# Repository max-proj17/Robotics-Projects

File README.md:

# Robotics Projects

Welcome to my Robotics Projects repository!  
This collection includes various robotics systems, simulations, and embedded applications.

Each project has its own dedicated folder and wiki page for documentation, code, and resources.
Click the link below!

[Wiki](https://github.com/max-proj17/Robotics-Projects/wiki)

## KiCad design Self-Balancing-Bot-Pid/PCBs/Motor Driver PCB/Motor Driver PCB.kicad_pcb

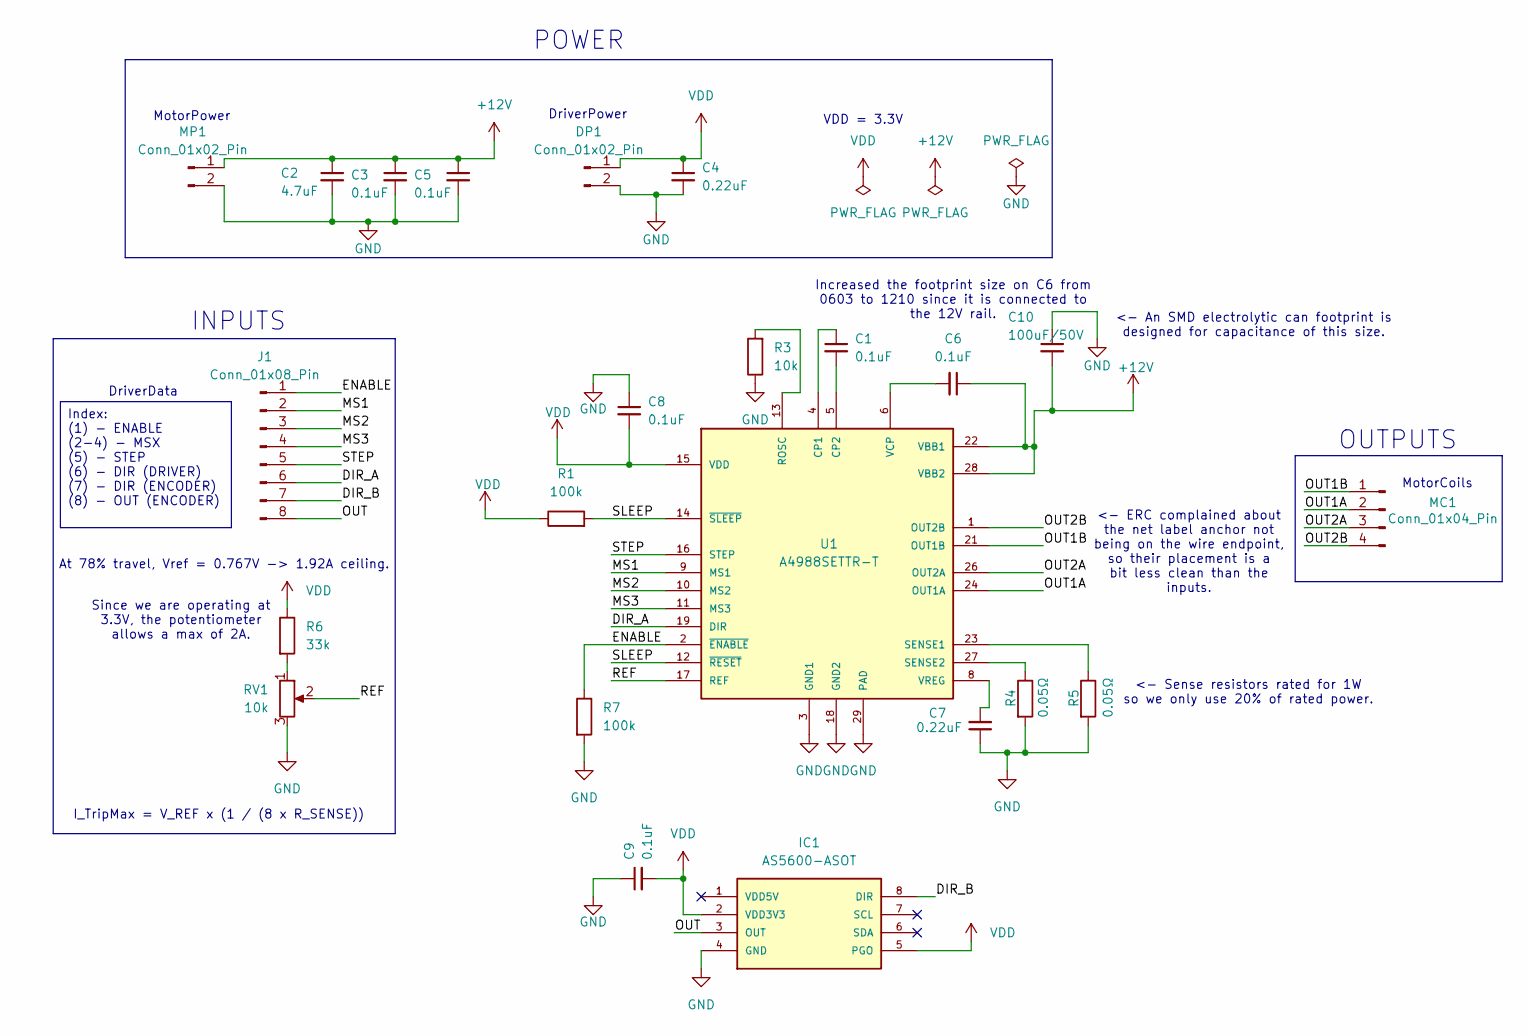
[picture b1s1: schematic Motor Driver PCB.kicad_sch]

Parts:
C1, C3, C5, C8, C9: 0.1uF; C_0603_1608Metric
C2: 4.7uF; C_0603_1608Metric
C4, C7: 0.22uF; C_0603_1608Metric
C6: 0.1uF; C_1210_3225Metric
C10: 100uF/50V; CP_Elec_8x10.5; MPN UWT1H101MNL1GS
DP1: Conn_01x02_Pin; JST_PH_B2B-PH-K_1x02_P2.00mm_Vertical
IC1: AS5600-ASOT; SOIC127P600X175-8N; MOUSER_PART_NUMBER 985-AS5600-ASOT
J1: Conn_01x08_Pin; JST_PH_B8B-PH-K_1x08_P2.00mm_Vertical
MC1: Conn_01x04_Pin; JST_PH_B4B-PH-K_1x04_P2.00mm_Vertical
MP1: Conn_01x02_Pin; JST_PH_B2B-PH-K_1x02_P2.00mm_Vertical
R1, R7: 100k; R_0603_1608Metric
R3: 10k; R_0603_1608Metric
R4, R5: 0.05Ω; R_2512_6332Metric; MPN WSL2512R0500FEA
R6: 33k; R_0603_1608Metric
RV1: 10k; Potentiometer_Bourns_3269W_Vertical
U1: A4988SETTR-T; QFN50P500X500X90-29N

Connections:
+12V: C2.1, C3.1, C5.1, C6.1, C10.2, MP1.1, U1.22 (VBB1), U1.28 (VBB2)
/DIR_A: J1.6, U1.19 (DIR)
/DIR_B: IC1.8 (DIR), J1.7
/ENABLE: J1.1, R7.1, U1.2 (~ENABLE)
/MS1: J1.2, U1.9 (MS1)
/MS2: J1.3, U1.10 (MS2)
/MS3: J1.4, U1.11 (MS3)
/OUT: IC1.3 (OUT), J1.8
/OUT1A: MC1.2, U1.24 (OUT1A)
/OUT1B: MC1.1, U1.21 (OUT1B)
/OUT2A: MC1.3, U1.26 (OUT2A)
/OUT2B: MC1.4, U1.1 (OUT2B)
/REF: RV1.2, U1.17 (REF)
/SLEEP: R1.2, U1.12 (~RESET), U1.14 (~SLEEP)
/STEP: J1.5, U1.16 (STEP)
GND: C2.2, C3.2, C4.2, C5.2, C7.1, C8.1, C9.1, C10.1, DP1.2, IC1.4 (GND), MP1.2, R3.1, R4.2, R5.2, R7.2, RV1.3, U1.3 (GND1), U1.18 (GND2), U1.29 (PAD)
unnamed: R6.2, RV1.1
unnamed: C1.1, U1.4 (CP1)
unnamed: C1.2, U1.5 (CP2)
unnamed: R3.2, U1.13 (ROSC)
unnamed: R5.1, U1.23 (SENSE1)
unnamed: R4.1, U1.27 (SENSE2)
unnamed: C6.2, U1.6 (VCP)
unnamed: C7.2, U1.8 (VREG)
VDD: C4.1, C8.2, C9.2, DP1.1, IC1.2 (VDD3V3), IC1.5 (PGO), R1.1, R6.1, U1.15 (VDD)

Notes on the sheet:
OUTPUTS
DriverData
MotorPower
At 78% travel, Vref = 0.767V -> 1.92A ceiling.
<- ERC complained about the net label anchor not being on the wire endpoint, so their placement is a bit less clean than the inputs.
<- Sense resistors rated for 1W so we only use 20% of rated power.
POWER
Increased the footprint size on C6 from 0603 to 1210 since it is connected to the 12V rail.
Since we are operating at 3.3V, the potentiometer allows a max of 2A.
DriverPower
MotorCoils
INPUTS
VDD = 3.3V
I_TripMax = V_REF x (1 / (8 x R_SENSE))
<- An SMD electrolytic can footprint is designed for capacitance of this size.
Index: (1) - ENABLE (2-4) - MSX (5) - STEP (6) - DIR (DRIVER) (7) - DIR (ENCODER) (8) - OUT (ENCODER)

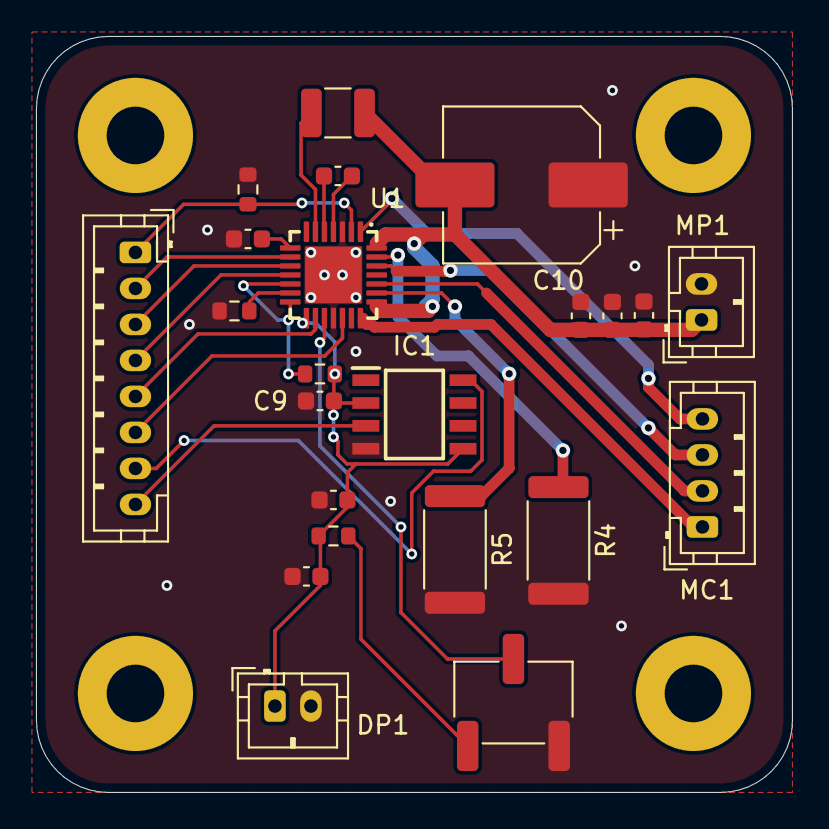
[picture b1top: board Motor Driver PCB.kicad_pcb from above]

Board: 2 copper layers, 42.0 x 42.0 mm, 27 parts (0 on the bottom side), 25 nets.

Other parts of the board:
Hole1, Hole2, Hole3, Hole4: MountingHole_3.2mm_M3_Pad

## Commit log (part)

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2025-04-11 Added arduino script to test driver and motor functionality at a high level
2025-04-12 Added encoder IC test. Had to add RC and software LPF because the sensor and onboard ADC is noisy
2025-04-12 Successfully integrated motor motion and encoder reading code. Next step is implementing FOC
2025-04-12 removed FOC for now because my motor driver does not have current sensing abilities. Will implement in the second version
2025-04-14 Started a test script for the IMU but the library is having issues
2025-04-15 Switched to a simpler library with a lot less overhead. Will not be using SPI or interrupts in this implementation. Maybe in v2 when I make compatible esp32s3 drivers myself.
2025-04-19 Working on chassis design now
2025-04-20 Started docker simulation environment creation
2025-04-20 Updated gitignore to remove uneeded files
2025-04-20 updated gitignore again with correct path
2025-04-20 Created working publisher and subscriber ros2 package within a docker container. Successfully setup development environment so I can run the docker containerfrom wsl in vscode on my host machine. Thi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
2025-04-22 Combined IMU and Encoder scripts into v1. Encodershave an offset value that I use so they are aligned with the IMU starting pitch
2025-04-23 Wrote xacro file and made it into a urdf. Still debugging why it isn't appearing in rviz
2025-04-24 Created urdf to resemble balancing bot size. Still need to fix the origins of the base, imu and encoders
2025-04-24 Completed full URDF with correct transforms
2025-04-24 realigned IMU
2025-04-25 My model loads in Gazebo! I also defined the mock hardware interface for the encoders and IMU.
2025-04-25 Slowing correcting the left and right wheel controllers. Focusing on the last couple dependency issues
2025-04-25 Almost have controllers working. Saving the progress I've made. Some params are in the wrong place
2025-04-28 edited dockerfile
2025-04-28 No more setup errors. Implementing controller node.
2025-04-29 refactored folder and package name
2025-04-29 Started kalman filter and PID implementation
2025-04-29 Fixed imu link probelm. Now just need to fix controller
2025-05-13 Added pause for the start and end of the gazebo simulation
2025-05-22 Fixed the imu publisher not starting issue. I just needed to use the default topic instead of my own. Focusing on fixing the timing of the physics now that the imu isnt the issue
2025-05-22 Forgot this file lol
2025-06-02 Starting attempt to latch CUDA to my docker instance
2025-06-02 Switched Cuda version docker container needs to download
2025-06-02 Fixing Dockerfile
2025-06-03 I am simply going to have commands to retrieve an updated ROS GPG key BEFORE calling apt update or upgrade
2025-06-03 The ros2 base image I reference already has a ros2.list referencing an old gpg key, so when I attempt to add a new ros2.list pointing to a different key, it conflicts and apt detects multiple entires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
2025-06-03 removed nvidia libraries because gpu is forwarded
2025-06-03 updated gitignore
2025-06-03 New simulation folder
2025-06-04 Created working pybullet simulation and plotting method. It is mulithreaded with a producer - consumer architecture
2025-06-04 Moved robot spawn position. Velocity PID is overreacting.
2025-06-05 Split all simulation components into different files. Figuring out if the Urdf or control laws are not correct
2025-06-05 Tuned the PID controller! Now I must thoroughly document all simulation code.
2025-06-07 Added angular velocity to the kalman filter. More stable results were observed
2025-12-08 Edited test files
2025-12-10 Started redesign of PCBs. Imported all footprints and symbols needed for motor driver
2025-12-15 Edited footprint of key components. Need to fix git ignore for auto gen files
2026-02-06 Completed a4988 IC integration
2026-02-07 Completed schematic, now working on pcb
2026-02-26 Removed devcontainer environment to run simulation on native linux
2026-02-28 Removed uneeded starter files. Stabilized urdf model. Fixed issue with gazebo_ros2_control not being initialized properly.
2026-03-02 Finsihed up controller tuning, and class restructuring for c++ code. Balance bot simulation complete!
2026-03-02 added image
2026-03-02 Add image of BalanceBot in Gazebo to README
2026-03-02 Remove BalanceBot image from README
    Removed the image of BalanceBot in Gazebo from README.
